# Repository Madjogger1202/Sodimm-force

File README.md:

# Sodimm-force rev0 
> [!IMPORTANT]
> Project wasn't produced and tested yet.
### Implementation of Orange Pi Zero 2W in sodimm form-factor

<table style="width: 100%; table-layout: fixed;">
  <tr>
    <td rowspan="4">
      
    </td>  
    <td rowspan="4">
      
    </td>  
  </tr>
</table>

## 🎲Revisions and logs:
<table>
  <tr>
    <td>
      <strong>Revision 0</strong>
    </td>   
    <td>
      <strong>10 March 2025</strong>
    </td> 
    <td>
      CPU H616, DDR MT53E1G32D2FW-046
    </td>
    <td>
      <strong>[x] not produced</strong>
    </td>
  </tr>
</table>

## 🧊 What Is This Project?

🐾 This entire project is just my take on an embedded compute module — but built around the Allwinner H616 SoC.

Not a clone. Not a dev board.  
Just **a compact, modular, SODIMM-sized brain** for custom systems. 💡

---

### 🛠️ The Vision

🐈 Made it to explore:
- How far can you push a **low-cost ARM SoC** in real embedded applications?
- Can we build something **industrial-grade**, yet **hackable and open**?
- What if your compute unit was **as easy to swap as RAM**?

So I said: *"Let’s make a tiny computer on a SODIMM."*  
And here we are. ✨

---

### 🔌 Key Features (SODIMM Form Factor)

- 🧩 **Modular by design** — plug into any carrier board
- 🧠 **Allwinner H616** — Quad-core Cortex-A53, Mali-G31 GPU, 4K@60 decoding
- 💾 **4GB LPDDR4** (Micron, automotive-grade) — fast & stable
- 💾 **microSD slot** — boot OS, store logs, update firmware
- 🖤 **EEPROM (ST M24M02)** — stores calibration, MAC, serials
- 📺 **0.96" IPS display (ST7735)** — built-in UI, no external screen needed
- 🔘 **4 tactile buttons** — navigate menus, trigger actions
- 🔌 **microHDMI 2.0** — 4K video out
- 🔌 **2× USB Type-C** — data, OTG, power
- ⚡ **DC-DC + LDO power** (SY8843QWC + SPX3819) — clean, efficient, stable
- 🛡️ **ESD protection** on all critical lines — because real world is harsh

---

### 🎯 Why H616?

🌟 Not the most powerful.  
🌟 Not the newest.  

But:
- ✅ **Mature Linux support** (Armbian, Debian, Buildroot)
- ✅ **Low power & heat** — perfect for fanless, compact designs
- ✅ **Full HDMI 2.0 + USB OTG** — rare at this price
- ✅ **Industrial temp RAM** — works where others fail
- ✅ **Open-ish ecosystem** — community-driven, no NDA hell

---

### 🧪 This Is a Prototype — Not Production

- 🚧 **Revision 0** — proof of concept
- ❌ `[x] not produced` — still not produced

## **˙✧˖°📷 ༘ ⋆｡˚ Stay tuned for further updates.˙✧˖°📷 ༘ ⋆｡˚**

### ***For any questions or collaborations i can be found on Telegram: [@madjogger](https://t.me/madjogger)***

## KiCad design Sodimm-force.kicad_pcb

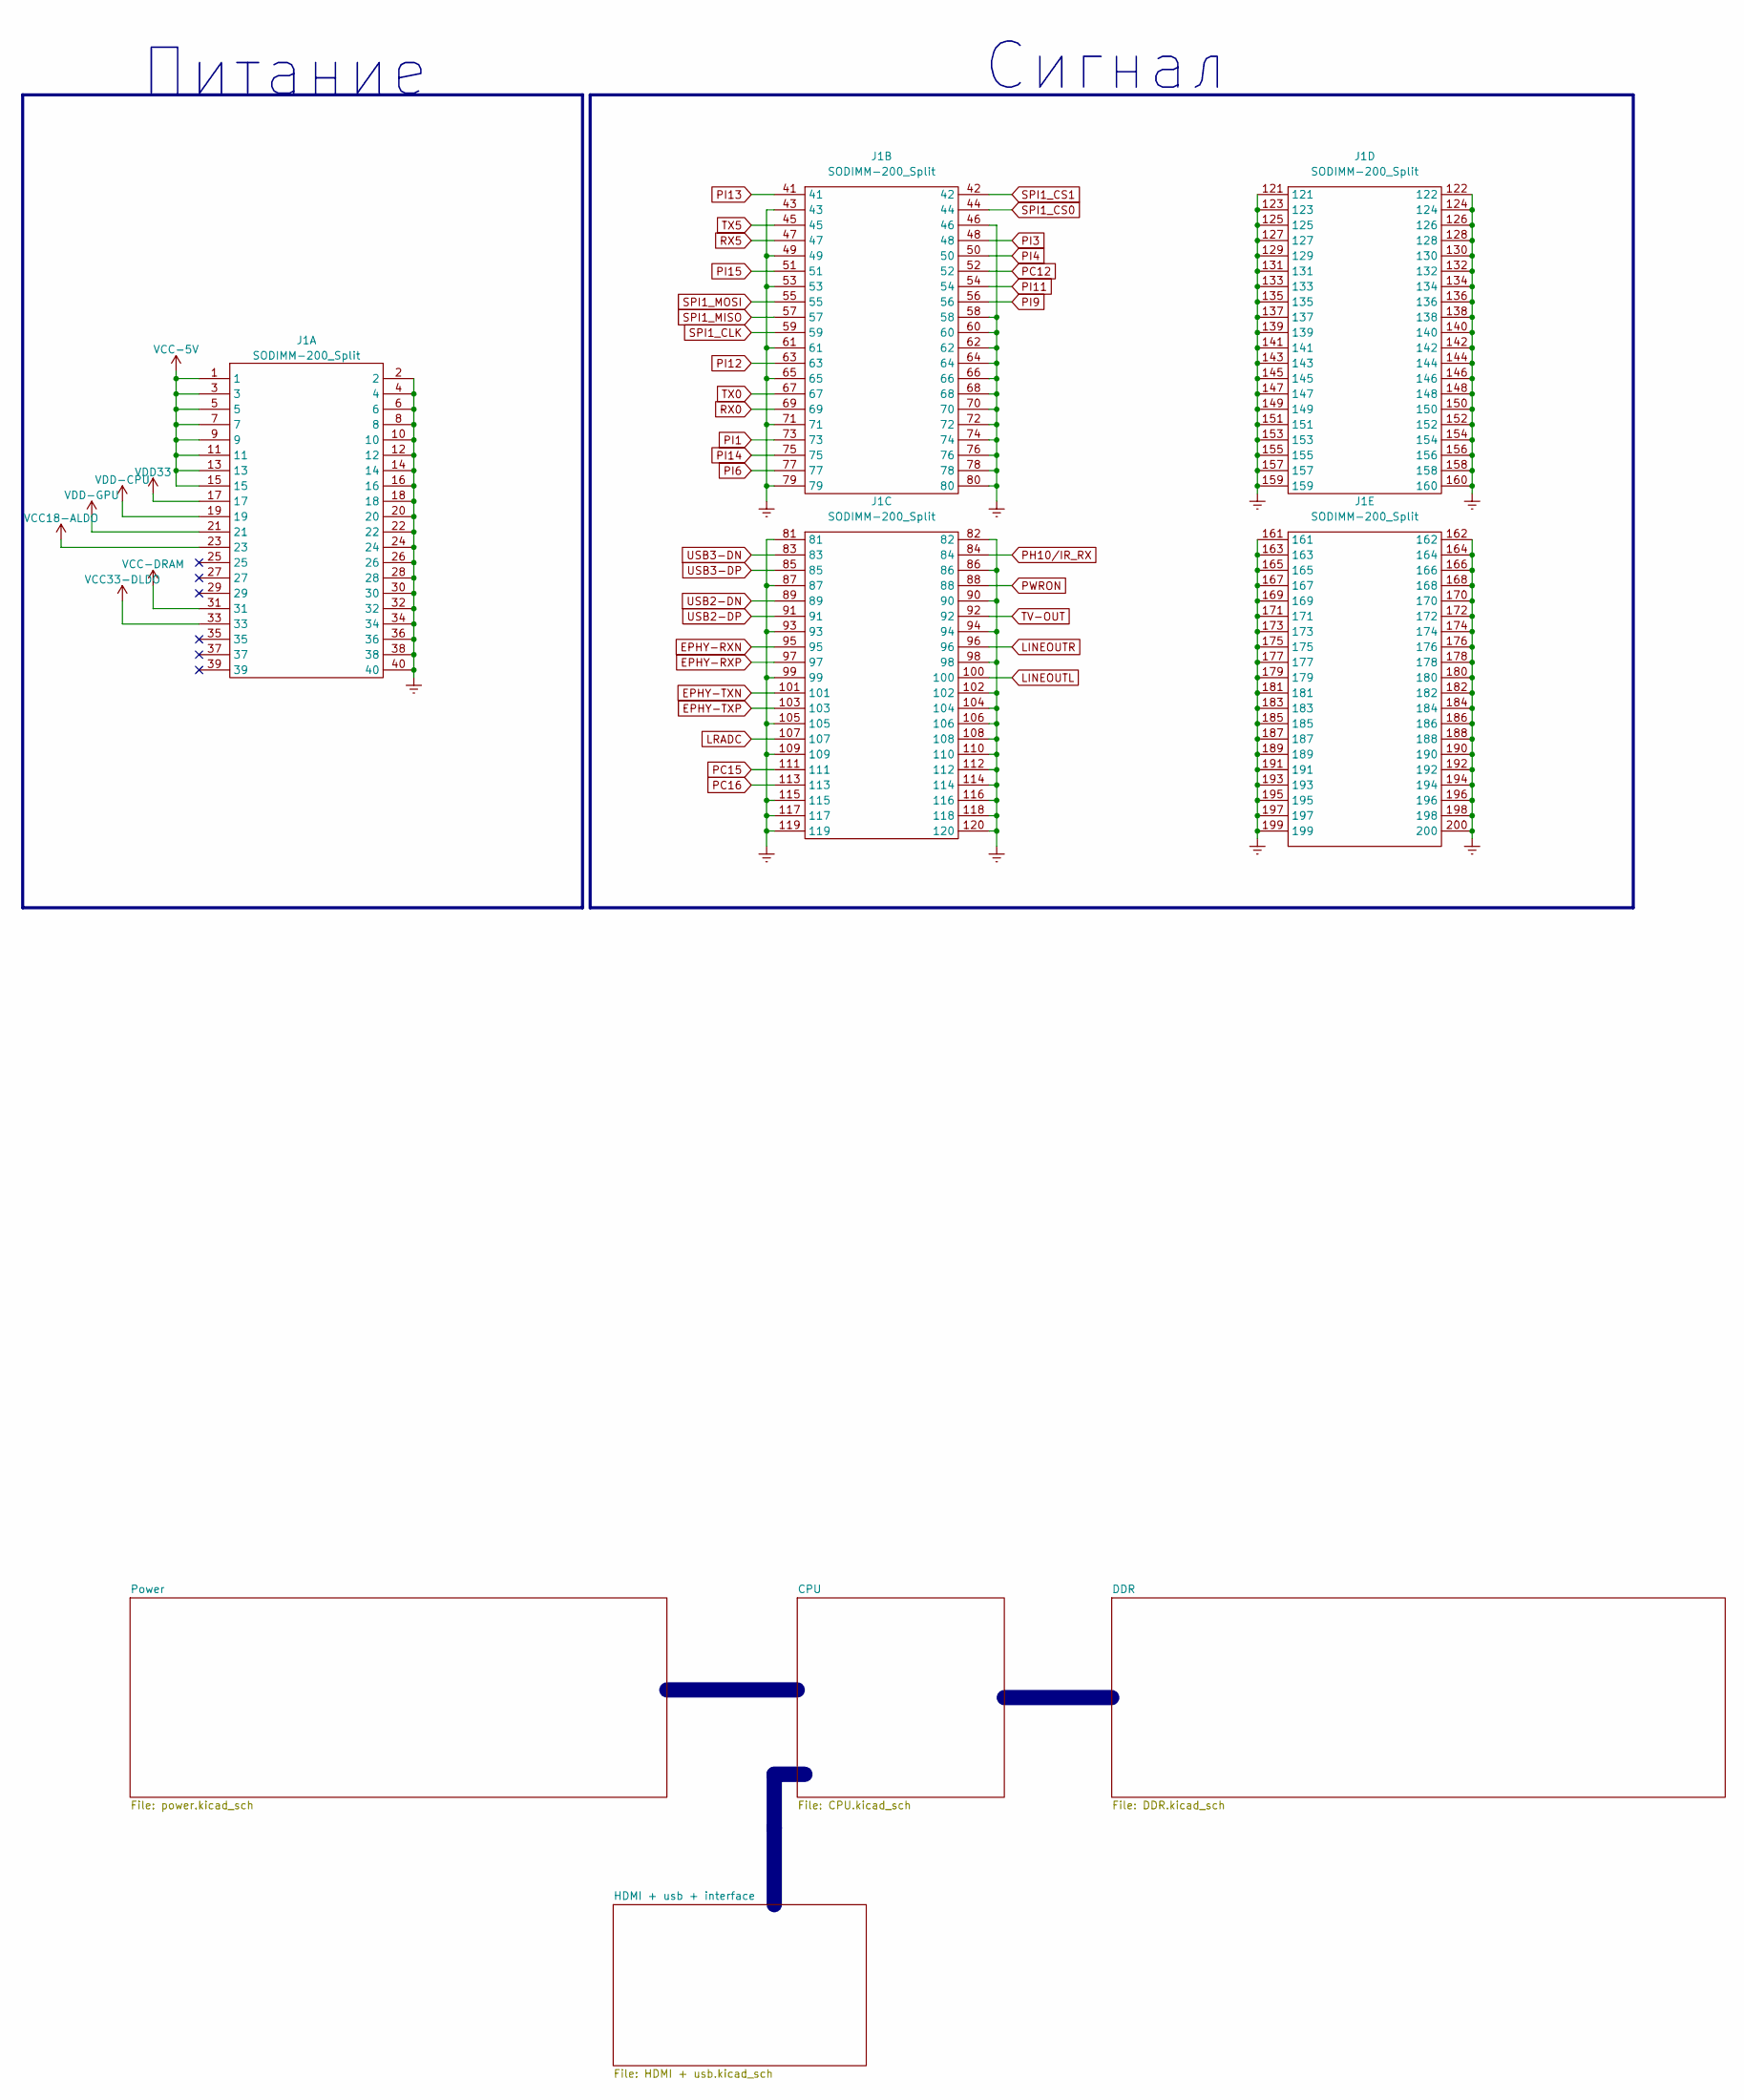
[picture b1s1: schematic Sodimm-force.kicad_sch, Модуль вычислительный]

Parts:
J1: SODIMM-200_Split; SODIMM-200_2.5V_Card_edge

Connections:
AVCC: J1.23; also elsewhere on the board
DCDCE: J1.17; also elsewhere on the board
EPHY-RXN: J1.95; also elsewhere on the board
EPHY-RXP: J1.97; also elsewhere on the board
EPHY-TXN: J1.101; also elsewhere on the board
EPHY-TXP: J1.103; also elsewhere on the board
Earth: J1.2, J1.4, J1.6, J1.8, J1.10, J1.12, J1.14, J1.16, J1.18, J1.20, J1.22, J1.24, J1.26, J1.28, J1.30, J1.32, J1.34, J1.36, J1.38, J1.40, J1.43, J1.46, J1.49, J1.53, J1.58, J1.60, J1.61, J1.62, J1.64, J1.65, J1.66, J1.68, J1.70, J1.71, J1.72, J1.74, J1.76, J1.78, J1.79, J1.80, J1.81, J1.82, J1.86, J1.87, J1.90, J1.93, J1.94, J1.98, J1.99, J1.102, J1.104, J1.105, J1.106, J1.108, J1.109, J1.110, J1.112, J1.114, J1.115, J1.116, J1.117, J1.118, J1.119, J1.120, J1.121, J1.122, J1.123, J1.124, J1.125, J1.126, J1.127, J1.128, J1.129, J1.130, J1.131, J1.132, J1.133, J1.134, J1.135, J1.136, J1.137, J1.138, J1.139, J1.140, J1.141, J1.142, J1.143, J1.144, J1.145, J1.146, J1.147, J1.148, J1.149, J1.150, J1.151, J1.152, J1.153, J1.154, J1.155, J1.156, J1.157, J1.158, J1.159, J1.160, J1.161, J1.162, J1.163, J1.164, J1.165, J1.166, J1.167, J1.168, J1.169, J1.170, J1.171, J1.172, J1.173, J1.174, J1.175, J1.176, J1.177, J1.178, J1.179, J1.180, J1.181, J1.182, J1.183, J1.184, J1.185, J1.186, J1.187, J1.188, J1.189, J1.190, J1.191, J1.192, J1.193, J1.194, J1.195, J1.196, J1.197, J1.198, J1.199, J1.200; also elsewhere on the board
LINEOUTL: J1.100; also elsewhere on the board
LINEOUTR: J1.96; also elsewhere on the board
LRADC: J1.107; also elsewhere on the board
PC12: J1.52; also elsewhere on the board
PC15: J1.111; also elsewhere on the board
PC16: J1.113; also elsewhere on the board
PI1: J1.73; also elsewhere on the board
PI3: J1.48; also elsewhere on the board
PI4: J1.50; also elsewhere on the board
PI6: J1.77; also elsewhere on the board
PI9: J1.56; also elsewhere on the board
PI11: J1.54; also elsewhere on the board
PI12: J1.63; also elsewhere on the board
PI13: J1.41; also elsewhere on the board
PI14: J1.75; also elsewhere on the board
PI15: J1.51; also elsewhere on the board
PWRON: J1.88
RX0: J1.69; also elsewhere on the board
RX5: J1.47; also elsewhere on the board
SPI1_CLK: J1.59; also elsewhere on the board
SPI1_CS0: J1.44; also elsewhere on the board
SPI1_CS1: J1.42; also elsewhere on the board
SPI1_MISO: J1.57; also elsewhere on the board
SPI1_MOSI: J1.55; also elsewhere on the board
TV-OUT: J1.92; also elsewhere on the board
TX0: J1.67; also elsewhere on the board
TX5: J1.45; also elsewhere on the board
USB2-DN: J1.89; also elsewhere on the board
USB2-DP: J1.91; also elsewhere on the board
USB3-DN: J1.83; also elsewhere on the board
USB3-DP: J1.85; also elsewhere on the board
VCC-5V: J1.1, J1.3, J1.5, J1.7, J1.9, J1.11, J1.13, J1.15; also elsewhere on the board
VCC-DRAM: J1.31; also elsewhere on the board
VCC-IO: J1.33; also elsewhere on the board
VDD-CPU: J1.19; also elsewhere on the board
VDD-GPU: J1.21; also elsewhere on the board

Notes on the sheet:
Сигнал
Питание

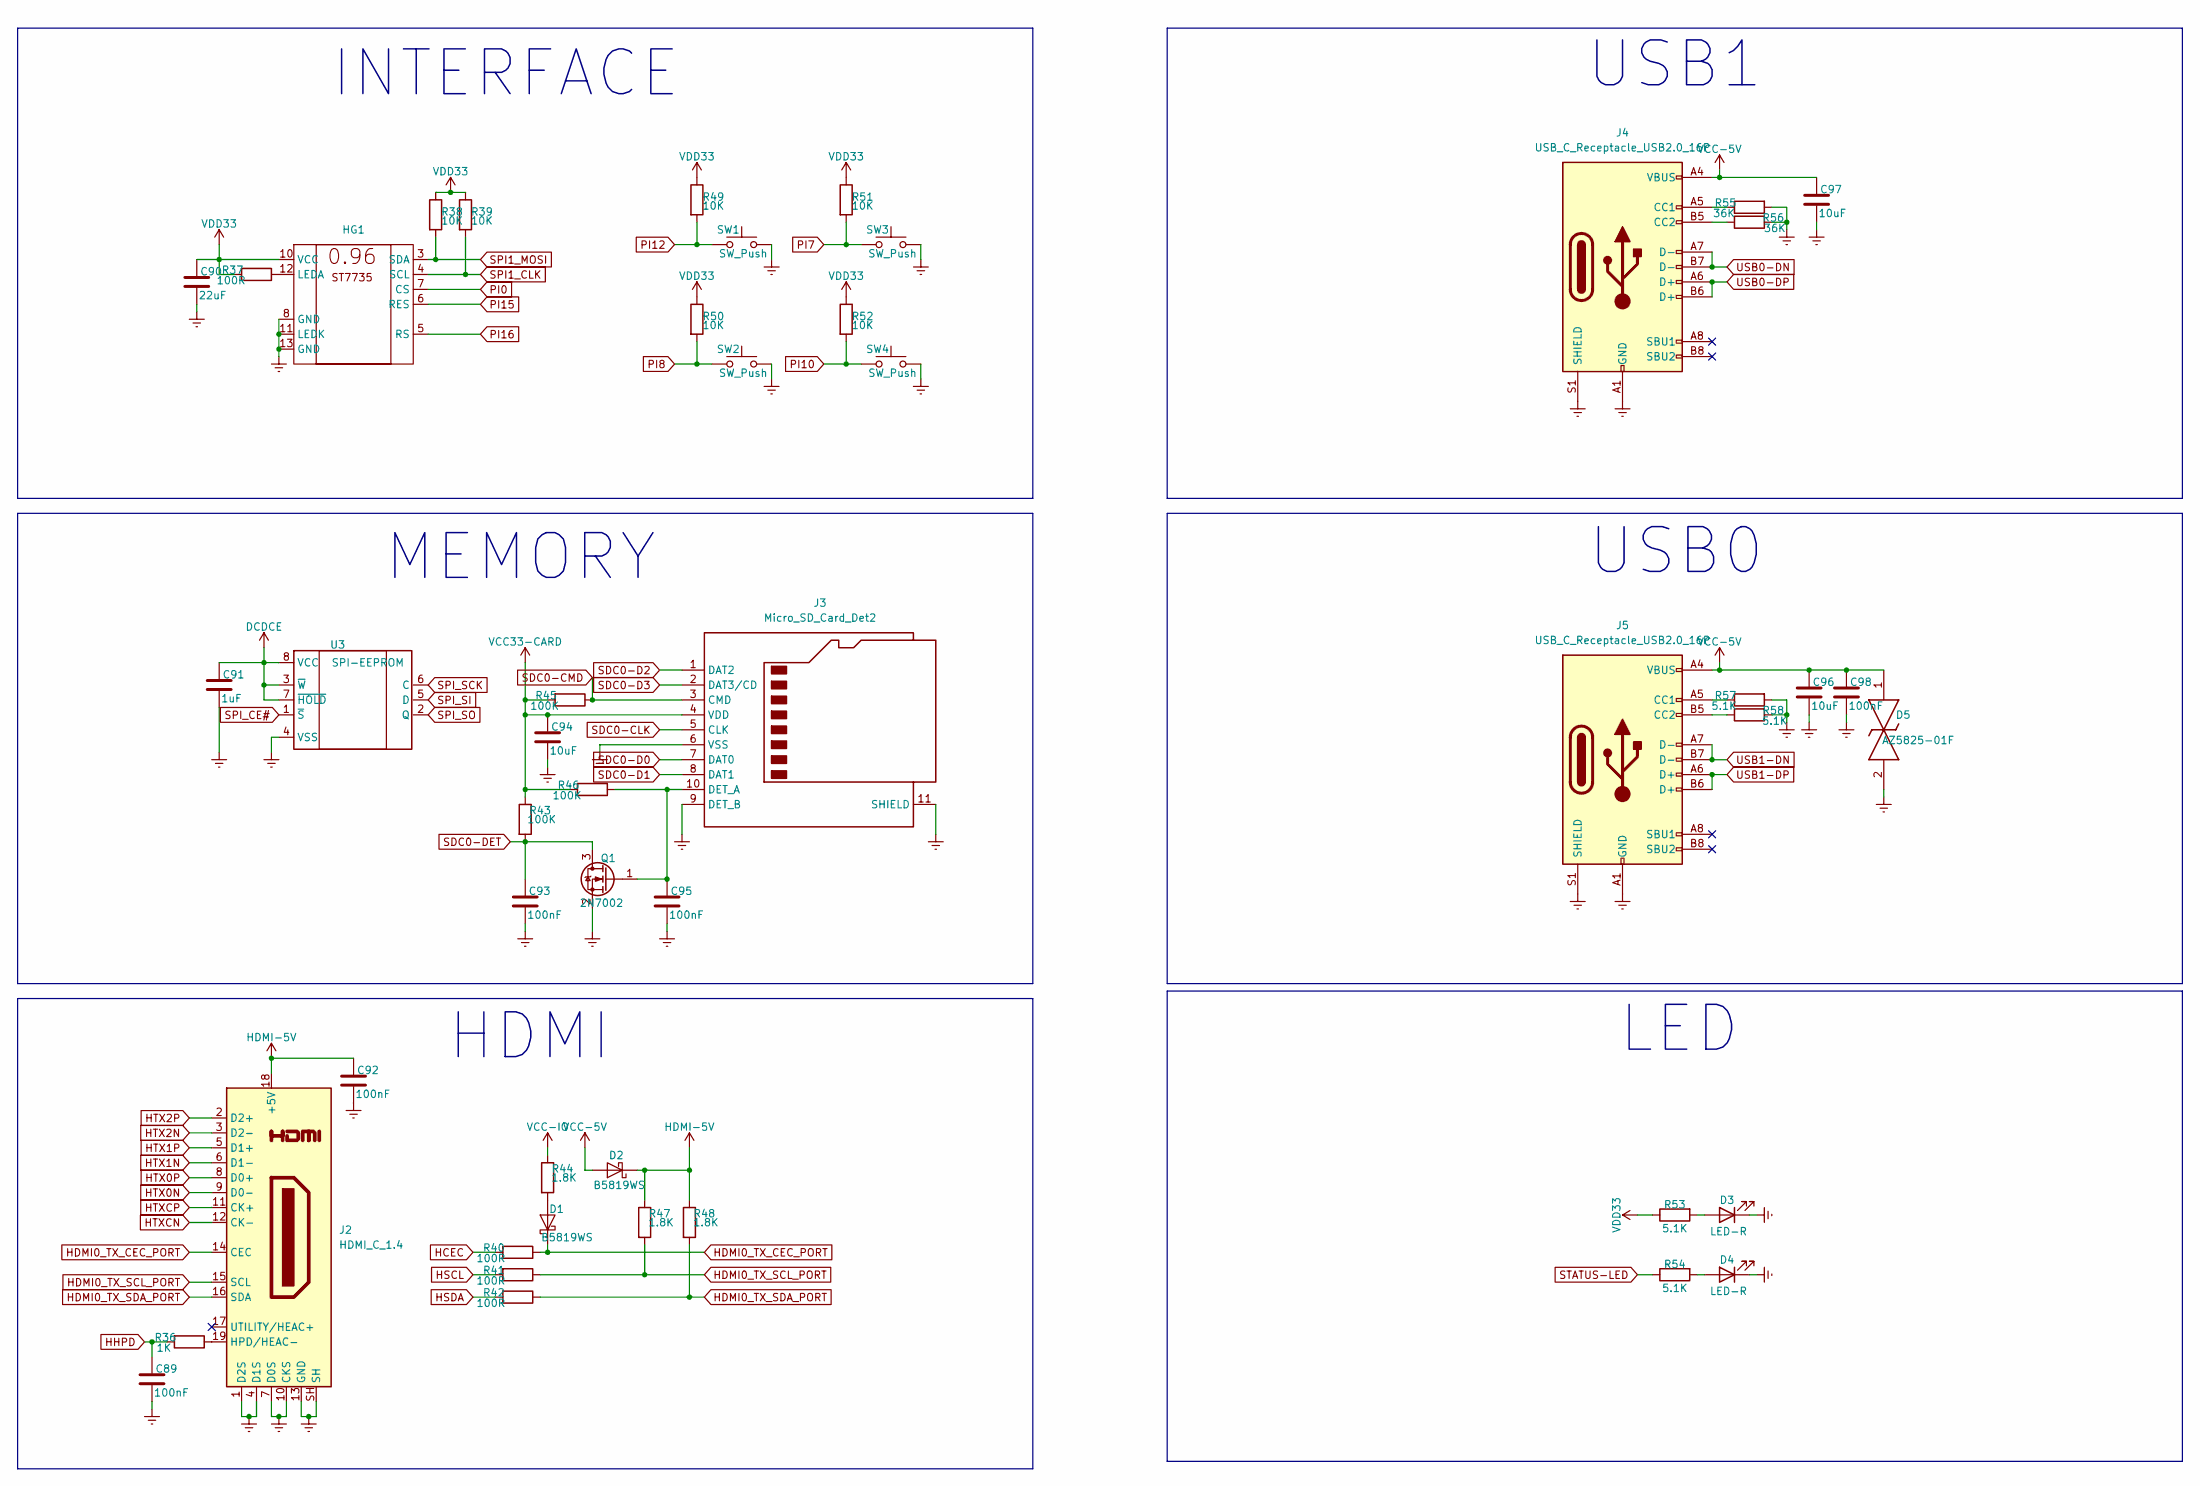
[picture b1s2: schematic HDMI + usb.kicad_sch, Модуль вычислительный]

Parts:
C89, C92, C93, C95, C98: 100nF; C_0402_1005Metric
C90: 22uF; C_0402_1005Metric
C91: 1uF; C_0402_1005Metric
C94, C96, C97: 10uF; C_0402_1005Metric
D1, D2: B5819WS; D_SOD-323F
D3, D4: LED-R; LED_0402_1005Metric
D5: AZ5825-01F; AZ582501F
HG1: ST7735 0.96
J2: HDMI_C_1.4; HDMI_Micro-D_Molex_46765-2x0x
J3: Micro_SD_Card_Det2; microSD_HC_Hirose_DM3AT-SF-PEJM5
J4, J5: USB_C_Receptacle_USB2.0_16P; USB_C_Receptacle_G-Switch_GT-USB-7010ASV
Q1: 2N7002; SOT-23
R36: 1K; R_0402_1005Metric
R37, R40, R41, R42: 100R; R_0402_1005Metric
R38, R39, R49, R50, R51, R52: 10K; R_0402_1005Metric
R43, R45, R46: 100K; R_0402_1005Metric
R44, R47, R48: 1.8K; R_0402_1005Metric
R53, R54, R57, R58: 5.1K; R_0402_1005Metric
R55, R56: 36K; R_0402_1005Metric
SW1, SW2, SW3, SW4: SW_Push; SW_Push_1P1T_NO_Vertical_Wuerth_434133025816
U3: SPI-EEPROM; SOIC-8_3.9x4.9mm_P1.27mm

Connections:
DCDCE: C90.1, C91.1, C94.1, HG1.10 (VCC), J3.4 (VDD), R37.2, R38.1, R39.1, R43.1, R45.2, R46.2, R49.1, R50.1, R51.1, R52.1, R53.1, U3.3 (~W), U3.7 (~HOLD), U3.8 (VCC); also elsewhere on the board
Earth: C89.2, C90.2, C91.2, C92.2, C93.2, C94.2, C95.2, C96.2, C97.2, C98.2, D3.1 (K), D4.1 (K), D5.2, HG1.8 (GND), HG1.11 (LEDK), HG1.13 (GND), J2.1 (D2S), J2.4 (D1S), J2.7 (D0S), J2.10 (CKS), J2.13 (GND), J2.SH, J3.6 (VSS), J3.9 (DET_B), J3.11 (SHIELD), J4.A1 (GND), J4.A12 (GND), J4.B1 (GND), J4.B12 (GND), J4.S1 (SHIELD), J5.A1 (GND), J5.A12 (GND), J5.B1 (GND), J5.B12 (GND), J5.S1 (SHIELD), Q1.2 (S), R55.2, R56.2, R57.2, R58.2, SW1.2, SW2.2, SW3.2, SW4.2, U3.4 (VSS); also elsewhere on the board
HCEC: R40.2; also elsewhere on the board
HDMI0_TX_CEC_PORT: D1.1 (K), J2.14 (CEC), R40.1
HDMI0_TX_SCL_PORT: J2.15 (SCL), R41.1, R47.2
HDMI0_TX_SDA_PORT: J2.16 (SDA), R42.1, R48.2
HDMI-5V: C92.1, D2.1 (K), J2.18 (+5V), R47.1, R48.1
HHPD: C89.1, R36.2; also elsewhere on the board
HSCL: R41.2; also elsewhere on the board
HSDA: R42.2; also elsewhere on the board
HTX0N: J2.9 (D0-); also elsewhere on the board
HTX0P: J2.8 (D0+); also elsewhere on the board
HTX1N: J2.6 (D1-); also elsewhere on the board
HTX1P: J2.5 (D1+); also elsewhere on the board
HTX2N: J2.3 (D2-); also elsewhere on the board
HTX2P: J2.2 (D2+); also elsewhere on the board
HTXCN: J2.12 (CK-); also elsewhere on the board
HTXCP: J2.11 (CK+); also elsewhere on the board
unnamed: D1.2 (A), R44.2
unnamed: D3.2 (A), R53.2
unnamed: D4.2 (A), R54.2
unnamed: HG1.12 (LEDA), R37.1
unnamed: J2.19 (HPD/HEAC-), R36.1
unnamed: C95.1, J3.10 (DET_A), Q1.1 (G), R46.1
unnamed: J4.A5 (CC1), R55.1
unnamed: J4.B5 (CC2), R56.1
unnamed: J5.A5 (CC1), R57.1
unnamed: J5.B5 (CC2), R58.1
PI0: HG1.7 (CS); also elsewhere on the board
PI7: R51.2, SW3.1; also elsewhere on the board
PI8: R50.2, SW2.1; also elsewhere on the board
PI10: R52.2, SW4.1; also elsewhere on the board
PI12: R49.2, SW1.1; also elsewhere on the board
PI15: HG1.6 (RES); also elsewhere on the board
PI16: HG1.5 (RS); also elsewhere on the board
SDC0-CLK: J3.5 (CLK); also elsewhere on the board
SDC0-CMD: J3.3 (CMD), R45.1; also elsewhere on the board
SDC0-D0: J3.7 (DAT0); also elsewhere on the board
SDC0-D1: J3.8 (DAT1); also elsewhere on the board
SDC0-D2: J3.1 (DAT2); also elsewhere on the board
SDC0-D3: J3.2 (DAT3/CD); also elsewhere on the board
SDC0-DET: C93.1, Q1.3 (D), R43.2; also elsewhere on the board
SPI0_CLK: U3.6 (C); also elsewhere on the board
SPI0_CS0: U3.1 (~S); also elsewhere on the board
SPI0_MISO: U3.2 (Q); also elsewhere on the board
SPI0_MOSI: U3.5 (D); also elsewhere on the board
SPI1_CLK: HG1.4 (SCL), R39.2; also elsewhere on the board
SPI1_MOSI: HG1.3 (SDA), R38.2; also elsewhere on the board
STATUS-LED: R54.1; also elsewhere on the board
USB0-DN: J4.A7 (D-), J4.B7 (D-); also elsewhere on the board
USB0-DP: J4.A6 (D+), J4.B6 (D+); also elsewhere on the board
USB1-DN: J5.A7 (D-), J5.B7 (D-); also elsewhere on the board
USB1-DP: J5.A6 (D+), J5.B6 (D+); also elsewhere on the board
VCC-5V: C96.1, C97.1, C98.1, D2.2 (A), D5.1, J4.A4 (VBUS), J4.A9 (VBUS), J4.B4 (VBUS), J4.B9 (VBUS), J5.A4 (VBUS), J5.A9 (VBUS), J5.B4 (VBUS), J5.B9 (VBUS); also elsewhere on the board
VCC-IO: R44.1; also elsewhere on the board

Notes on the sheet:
USB1
INTERFACE
LED
USB0
MEMORY
HDMI

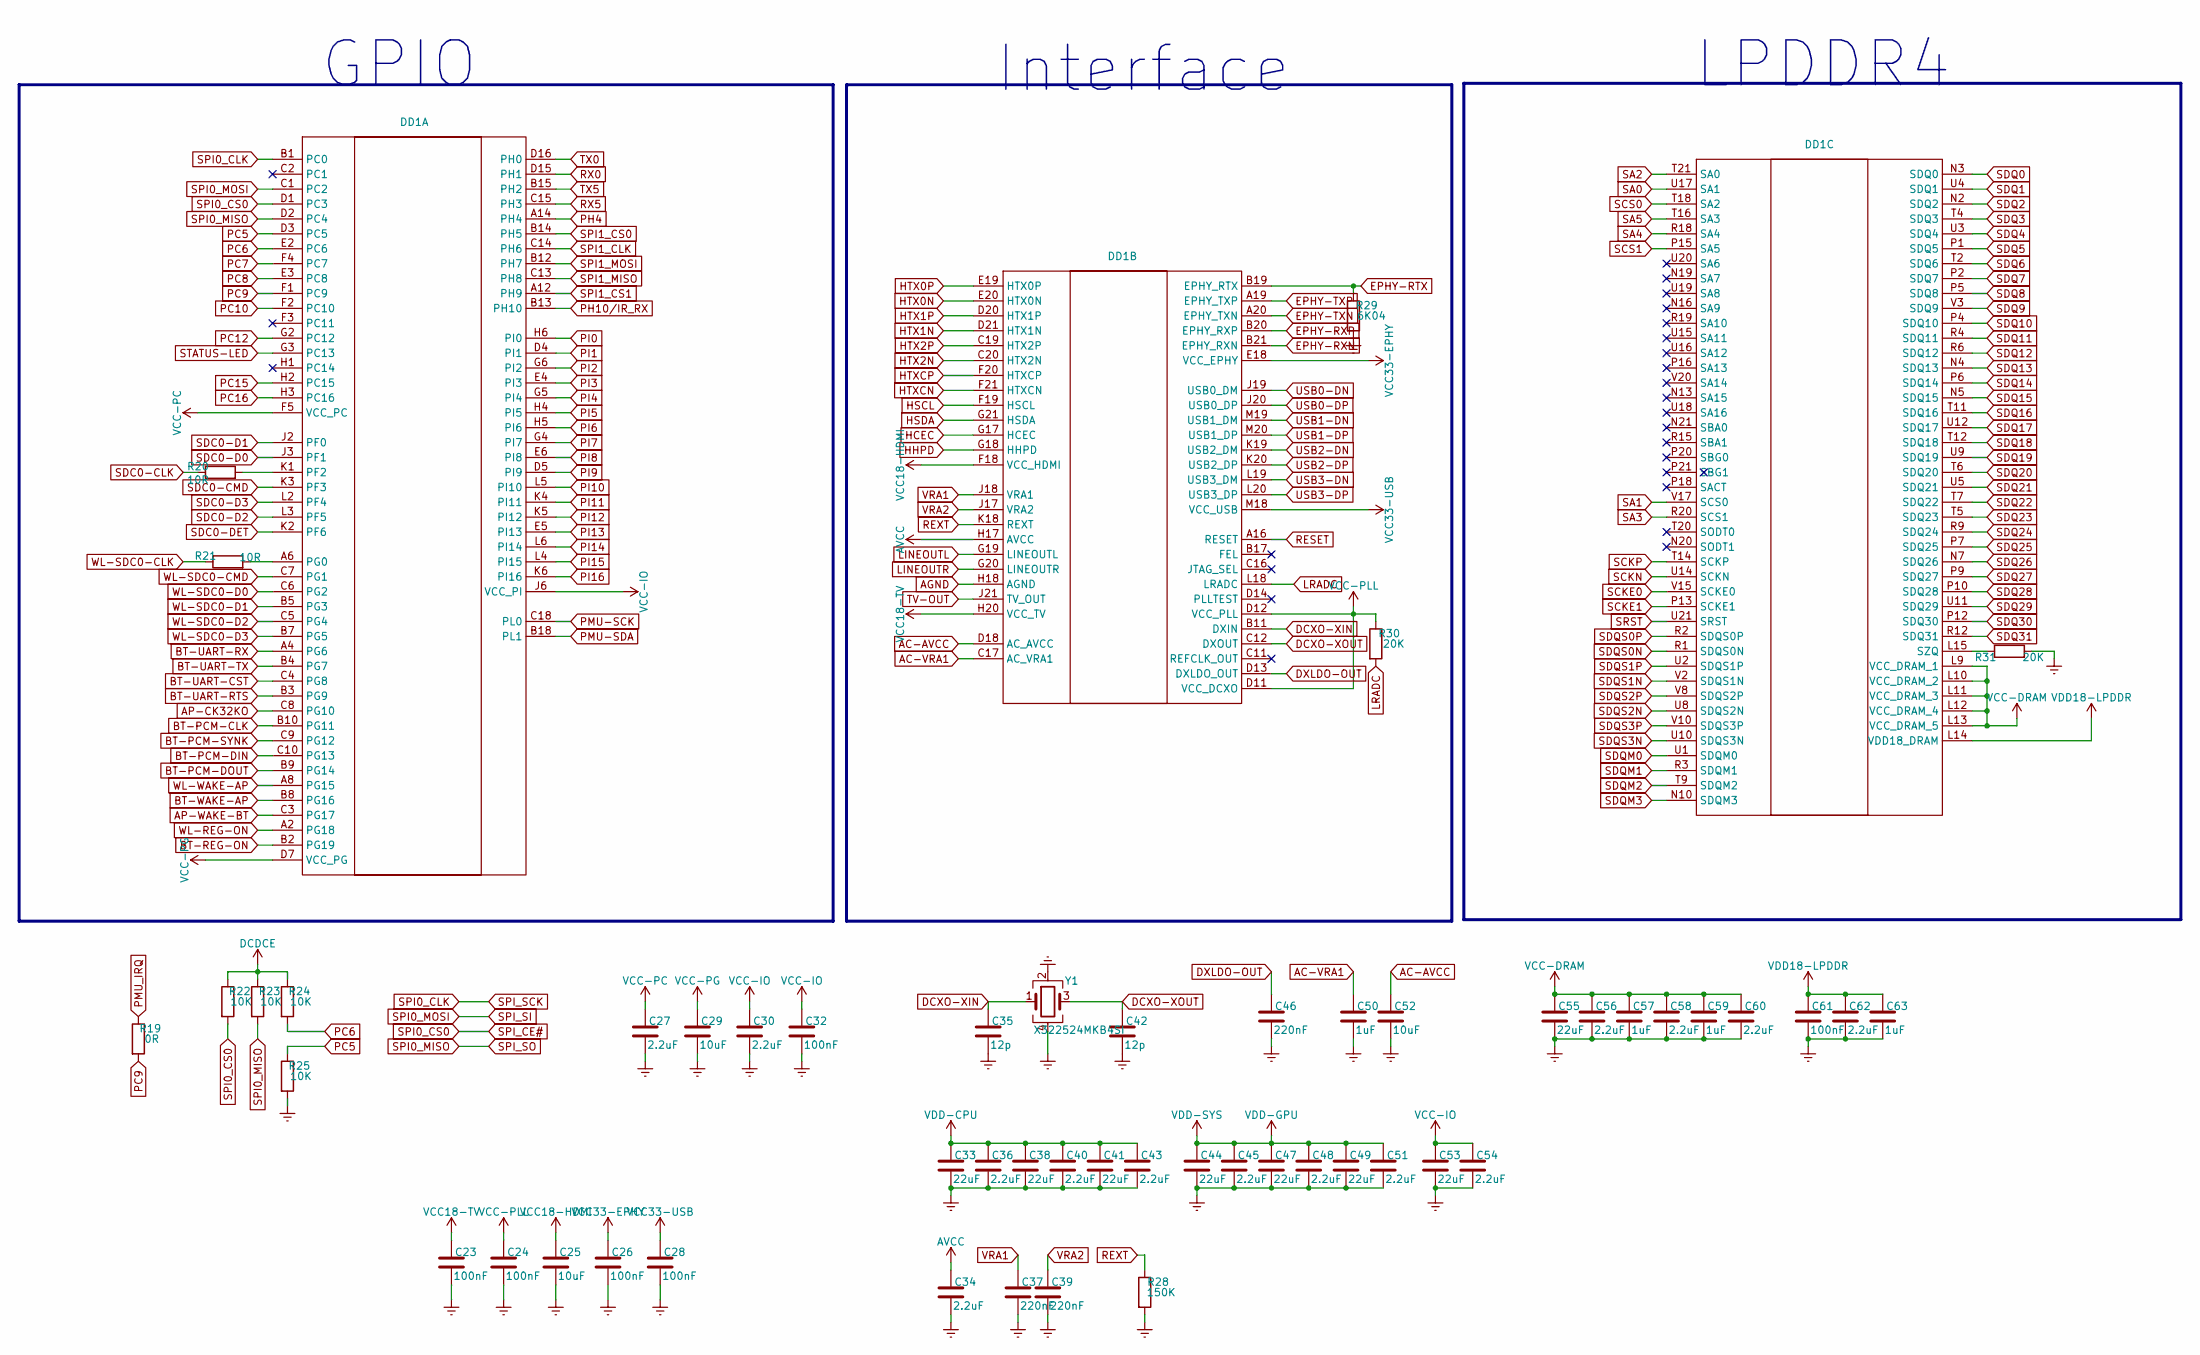
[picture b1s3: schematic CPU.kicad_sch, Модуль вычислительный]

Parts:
C23, C24, C26, C28, C32, C61: 100nF; C_0402_1005Metric
C25, C29, C52: 10uF; C_0402_1005Metric
C27, C30, C34, C36, C40, C43, C45, C48, C51, C54, C56, C58, C60, C62: 2.2uF; C_0402_1005Metric
C33, C38, C41, C44, C47, C49, C53, C55: 22uF; C_0402_1005Metric
C35, C42: 12p; C_0402_1005Metric
C37, C39, C46: 220nF; C_0402_1005Metric
C50, C57, C59, C63: 1uF; C_0402_1005Metric
DD1: H616
R19: 0R; R_0402_1005Metric
R20, R21: 10R; R_0402_1005Metric
R22, R23, R24, R25: 10K; R_0402_1005Metric
R28: 150K; R_0402_1005Metric
R29: 6K04; R_0402_1005Metric
R30, R31: 20K; R_0402_1005Metric
Y1: X322524MKB4SI; Oscillator_SMD_EuroQuartz_XO32-4Pin_3.2x2.5mm

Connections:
AC-AVCC: C52.1, DD1.D18 (AC_AVCC)
AC-VRA1: C50.1, DD1.C17 (AC_VRA1)
AGND: DD1.H18 (AGND)
AP-CK32KO: DD1.C8 (PG10)
AP-WAKE-BT: DD1.C3 (PG17)
AVCC: C23.1, C24.1, C25.1, C29.1, C34.1, C61.1, C62.1, C63.1, DD1.D7 (VCC_PG), DD1.D11 (VCC_DCXO), DD1.D12 (VCC_PLL), DD1.F18 (VCC_HDMI), DD1.H17 (AVCC), DD1.H20 (VCC_TV), DD1.L14 (VDD18_DRAM), R30.1; also elsewhere on the board
BT-PCM-CLK: DD1.B10 (PG11)
BT-PCM-DIN: DD1.C10 (PG13)
BT-PCM-DOUT: DD1.B9 (PG14)
BT-PCM-SYNK: DD1.C9 (PG12)
BT-REG-ON: DD1.B2 (PG19)
BT-UART-CST: DD1.C4 (PG8)
BT-UART-RTS: DD1.B3 (PG9)
BT-UART-RX: DD1.A4 (PG6)
BT-UART-TX: DD1.B4 (PG7)
BT-WAKE-AP: DD1.B8 (PG16)
DCDCE: R22.1, R23.1, R24.1; also elsewhere on the board
DCXO-XIN: C35.1, DD1.B11 (DXIN), Y1.1
DCXO-XOUT: C42.1, DD1.C12 (DXOUT), Y1.3
DXLDO-OUT: C46.1, DD1.D13 (DXLDO_OUT)
EPHY-RTX: DD1.B19 (EPHY_RTX), R29.1
EPHY-RXN: DD1.B21 (EPHY_RXN); also elsewhere on the board
EPHY-RXP: DD1.B20 (EPHY_RXP); also elsewhere on the board
EPHY-TXN: DD1.A20 (EPHY_TXN); also elsewhere on the board
EPHY-TXP: DD1.A19 (EPHY_TXP); also elsewhere on the board
Earth: C23.2, C24.2, C25.2, C26.2, C27.2, C28.2, C29.2, C30.2, C32.2, C33.2, C34.2, C35.2, C36.2, C37.2, C38.2, C39.2, C40.2, C41.2, C42.2, C43.2, C44.2, C45.2, C46.2, C47.2, C48.2, C49.2, C50.2, C51.2, C52.2, C53.2, C54.2, C55.2, C56.2, C57.2, C58.2, C59.2, C60.2, C61.2, C62.2, C63.2, R25.2, R28.2, R29.2, R31.2, Y1.2, Y1.4; also elsewhere on the board
HCEC: DD1.G17 (HCEC); also elsewhere on the board
HHPD: DD1.G18 (HHPD); also elsewhere on the board
HSCL: DD1.F19 (HSCL); also elsewhere on the board
HSDA: DD1.G21 (HSDA); also elsewhere on the board
HTX0N: DD1.E20 (HTX0N); also elsewhere on the board
HTX0P: DD1.E19 (HTX0P); also elsewhere on the board
HTX1N: DD1.D21 (HTX1N); also elsewhere on the board
HTX1P: DD1.D20 (HTX1P); also elsewhere on the board
HTX2N: DD1.C20 (HTX2N); also elsewhere on the board
HTX2P: DD1.C19 (HTX2P); also elsewhere on the board
HTXCN: DD1.F21 (HTXCN); also elsewhere on the board
HTXCP: DD1.F20 (HTXCP); also elsewhere on the board
LINEOUTL: DD1.G19 (LINEOUTL); also elsewhere on the board
LINEOUTR: DD1.G20 (LINEOUTR); also elsewhere on the board
LRADC: DD1.L18 (LRADC), R30.2; also elsewhere on the board
unnamed: DD1.K1 (PF2), R20.2
unnamed: DD1.A6 (PG0), R21.2
unnamed: DD1.L15 (SZQ), R31.1
PC5: DD1.D3 (PC5), R25.1
PC6: DD1.E2 (PC6), R24.2
PC7: DD1.F4 (PC7)
PC8: DD1.E3 (PC8)
PC9: DD1.F1 (PC9), R19.2
PC10: DD1.F2 (PC10)
PC12: DD1.G2 (PC12); also elsewhere on the board
PC15: DD1.H2 (PC15); also elsewhere on the board
PC16: DD1.H3 (PC16); also elsewhere on the board
PH4: DD1.A14 (PH4)
PI0: DD1.H6 (PI0); also elsewhere on the board
PI1: DD1.D4 (PI1); also elsewhere on the board
PI2: DD1.G6 (PI2)
PI3: DD1.E4 (PI3); also elsewhere on the board
PI4: DD1.G5 (PI4); also elsewhere on the board
PI5: DD1.H4 (PI5)
PI6: DD1.H5 (PI6); also elsewhere on the board
PI7: DD1.G4 (PI7); also elsewhere on the board
PI8: DD1.E6 (PI8); also elsewhere on the board
PI9: DD1.D5 (PI9); also elsewhere on the board
PI10: DD1.L5 (PI10); also elsewhere on the board
PI11: DD1.K4 (PI11); also elsewhere on the board
PI12: DD1.K5 (PI12); also elsewhere on the board
PI13: DD1.E5 (PI13); also elsewhere on the board
PI14: DD1.L6 (PI14); also elsewhere on the board
PI15: DD1.L4 (PI15); also elsewhere on the board
PI16: DD1.K6 (PI16); also elsewhere on the board
PMU-SCK: DD1.C18 (PL0)
PMU-SDA: DD1.B18 (PL1)
PMU_IRQ: R19.1
RESET: DD1.A16 (RESET)
REXT: DD1.K18 (REXT), R28.1
RX0: DD1.D15 (PH1); also elsewhere on the board
RX5: DD1.C15 (PH3); also elsewhere on the board
SA0: DD1.U17 (SA1); also elsewhere on the board
SA1: DD1.V17 (SCS0); also elsewhere on the board
SA2: DD1.T21 (SA0); also elsewhere on the board
SA3: DD1.R20 (SCS1); also elsewhere on the board
SA4: DD1.R18 (SA4); also elsewhere on the board
SA5: DD1.T16 (SA3); also elsewhere on the board
SCKE0: DD1.V15 (SCKE0); also elsewhere on the board
SCKE1: DD1.P13 (SCKE1); also elsewhere on the board
SCKN: DD1.U14 (SCKN); also elsewhere on the board
SCKP: DD1.T14 (SCKP); also elsewhere on the board
SCS0: DD1.T18 (SA2); also elsewhere on the board
SCS1: DD1.P15 (SA5); also elsewhere on the board
SDC0-CLK: R20.1; also elsewhere on the board
SDC0-CMD: DD1.K3 (PF3); also elsewhere on the board
SDC0-D0: DD1.J3 (PF1); also elsewhere on the board
SDC0-D1: DD1.J2 (PF0); also elsewhere on the board
SDC0-D2: DD1.L3 (PF5); also elsewhere on the board
SDC0-D3: DD1.L2 (PF4); also elsewhere on the board
SDC0-DET: DD1.K2 (PF6); also elsewhere on the board
SDQ0: DD1.N3 (SDQ0); also elsewhere on the board
SDQ1: DD1.U4 (SDQ1); also elsewhere on the board
SDQ2: DD1.N2 (SDQ2); also elsewhere on the board
SDQ3: DD1.T4 (SDQ3); also elsewhere on the board
SDQ4: DD1.U3 (SDQ4); also elsewhere on the board
SDQ5: DD1.P1 (SDQ5); also elsewhere on the board
SDQ6: DD1.T2 (SDQ6); also elsewhere on the board
SDQ7: DD1.P2 (SDQ7); also elsewhere on the board
SDQ8: DD1.P5 (SDQ8); also elsewhere on the board
SDQ9: DD1.V3 (SDQ9); also elsewhere on the board
SDQ10: DD1.P4 (SDQ10); also elsewhere on the board
SDQ11: DD1.R4 (SDQ11); also elsewhere on the board
SDQ12: DD1.R6 (SDQ12); also elsewhere on the board
SDQ13: DD1.N4 (SDQ13); also elsewhere on the board
SDQ14: DD1.P6 (SDQ14); also elsewhere on the board
SDQ15: DD1.N5 (SDQ15); also elsewhere on the board
SDQ16: DD1.T11 (SDQ16); also elsewhere on the board
SDQ17: DD1.U12 (SDQ17); also elsewhere on the board
SDQ18: DD1.T12 (SDQ18); also elsewhere on the board
SDQ19: DD1.U9 (SDQ19); also elsewhere on the board
SDQ20: DD1.T6 (SDQ20); also elsewhere on the board
SDQ21: DD1.U5 (SDQ21); also elsewhere on the board
SDQ22: DD1.T7 (SDQ22); also elsewhere on the board
SDQ23: DD1.T5 (SDQ23); also elsewhere on the board
SDQ24: DD1.R9 (SDQ24); also elsewhere on the board
SDQ25: DD1.P7 (SDQ25); also elsewhere on the board
SDQ26: DD1.N7 (SDQ26); also elsewhere on the board
SDQ27: DD1.P9 (SDQ27); also elsewhere on the board
SDQ28: DD1.P10 (SDQ28); also elsewhere on the board
SDQ29: DD1.U11 (SDQ29); also elsewhere on the board
SDQ30: DD1.P12 (SDQ30); also elsewhere on the board
SDQ31: DD1.R12 (SDQ31); also elsewhere on the board
SDQM0: DD1.U1 (SDQM0); also elsewhere on the board
SDQM1: DD1.R3 (SDQM1); also elsewhere on the board
SDQM2: DD1.T9 (SDQM2); also elsewhere on the board
SDQM3: DD1.N10 (SDQM3); also elsewhere on the board
SDQS0N: DD1.R1 (SDQS0N); also elsewhere on the board
SDQS0P: DD1.R2 (SDQS0P); also elsewhere on the board
SDQS1N: DD1.V2 (SDQS1N); also elsewhere on the board
SDQS1P: DD1.U2 (SDQS1P); also elsewhere on the board
SDQS2N: DD1.U8 (SDQS2N); also elsewhere on the board
SDQS2P: DD1.V8 (SDQS2P); also elsewhere on the board
SDQS3N: DD1.U10 (SDQS3N); also elsewhere on the board
SDQS3P: DD1.V10 (SDQS3P); also elsewhere on the board
SPI0_CLK: DD1.B1 (PC0); also elsewhere on the board
SPI0_CS0: DD1.D1 (PC3), R22.2; also elsewhere on the board
SPI0_MISO: DD1.D2 (PC4), R23.2; also elsewhere on the board
SPI0_MOSI: DD1.C1 (PC2); also elsewhere on the board
SPI1_CLK: DD1.C14 (PH6); also elsewhere on the board
SPI1_CS0: DD1.B14 (PH5); also elsewhere on the board
SPI1_CS1: DD1.A12 (PH9); also elsewhere on the board
SPI1_MISO: DD1.C13 (PH8); also elsewhere on the board
SPI1_MOSI: DD1.B12 (PH7); also elsewhere on the board
SRST: DD1.U21 (SRST); also elsewhere on the board
STATUS-LED: DD1.G3 (PC13); also elsewhere on the board
TV-OUT: DD1.J21 (TV_OUT); also elsewhere on the board
TX0: DD1.D16 (PH0); also elsewhere on the board
TX5: DD1.B15 (PH2); also elsewhere on the board
USB0-DN: DD1.J19 (USB0_DM); also elsewhere on the board
USB0-DP: DD1.J20 (USB0_DP); also elsewhere on the board
USB1-DN: DD1.M19 (USB1_DM); also elsewhere on the board
USB1-DP: DD1.M20 (USB1_DP); also elsewhere on the board
USB2-DN: DD1.K19 (USB2_DM); also elsewhere on the board
USB2-DP: DD1.K20 (USB2_DP); also elsewhere on the board
USB3-DN: DD1.L19 (USB3_DM); also elsewhere on the board
USB3-DP: DD1.L20 (USB3_DP); also elsewhere on the board
VCC-DRAM: C55.1, C56.1, C57.1, C58.1, C59.1, C60.1, DD1.L9 (VCC_DRAM_1), DD1.L10 (VCC_DRAM_2), DD1.L11 (VCC_DRAM_3), DD1.L12 (VCC_DRAM_4), DD1.L13 (VCC_DRAM_5); also elsewhere on the board
VCC-IO: C26.1, C27.1, C28.1, C30.1, C32.1, C53.1, C54.1, DD1.E18 (VCC_EPHY), DD1.F5 (VCC_PC), DD1.J6 (VCC_PI), DD1.M18 (VCC_USB); also elsewhere on the board
VDD-CPU: C33.1, C36.1, C38.1, C40.1, C41.1, C43.1; also elsewhere on the board
VDD-GPU: C44.1, C45.1, C47.1, C48.1, C49.1, C51.1; also elsewhere on the board
VRA1: C37.1, DD1.J18 (VRA1)
VRA2: C39.1, DD1.J17 (VRA2)
WL-REG-ON: DD1.A2 (PG18)
WL-SDC0-CLK: R21.1
WL-SDC0-CMD: DD1.C7 (PG1)
WL-SDC0-D0: DD1.C6 (PG2)
WL-SDC0-D1: DD1.B5 (PG3)
WL-SDC0-D2: DD1.C5 (PG4)
WL-SDC0-D3: DD1.B7 (PG5)
WL-WAKE-AP: DD1.A8 (PG15)

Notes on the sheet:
LPDDR4
Interface
GPIO
